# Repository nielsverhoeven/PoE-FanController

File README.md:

# PoE-FanController

A PoE 802.3at (25.5 W) powered quad-fan controller using the **Waveshare ESP32-P4-ETH**
development board (SKU 32086) mounted HAT-style on a custom carrier PCB.  The carrier
handles PoE power extraction and 12 V fan outputs; the Waveshare module integrates the
**ESP32-P4NRW32** SoC, **LAN8720A** Ethernet PHY (RMII), **CH343P** USB-UART bridge,
USB-C connector, and 32 MB flash + 32 MB PSRAM.  Provides wired Ethernet for reliable
data-centre and server-room deployments.

## Key components

| Ref | Part | Function |
|-----|------|----------|
| —   | Waveshare ESP32-P4-ETH (SKU 32086) | MCU module — ESP32-P4NRW32 dual-core RISC-V 400 MHz, LAN8720A PHY, CH343P USB bridge, 32 MB flash, 32 MB PSRAM |
| J8  | Sullins PREC020DAAN-RC / Würth 61304021821 | 2×20 HAT header — carrier PCB ↔ Waveshare module |
| U1  | Ag9905M (Silvertel) | PoE+ PD module — 802.3at Class 4, 12 V isolated output |
| U2  | LM2596S-5.0/NOPB (TI) | Buck regulator — 12 V → 5 V, 3 A |
| D2  | 1N5822 | USB back-feed protection Schottky — prevents back-feeding PC USB host when Waveshare is programmed via USB-C while PoE is live |
| J1  | Würth 615008144521 | Shielded RJ45 — PoE **power** input only; MDI secondary NC |

## Features

- 4 × 12 V PWM fan channels (25 kHz), GPIO4–7
- 4 × tachometer inputs (IRAM_ATTR ISR), GPIO8–11
- NTC thermistor ADC (GPIO16, 12-bit)
- HTTP OTA firmware update via POST `/api/v1/ota`
- Wired Ethernet via Waveshare's built-in LAN8720A (ETH.begin() / RMII)
- PoE 802.3at Class 4 power budget: ~18.9 W consumed; ~1.1 W margin against 20 W cap
- Programming and debug via Waveshare's USB-C connector (CH343P USB-UART bridge)

## Power supply

```
J1 RJ45 (PoE power only, MDI secondary NC)
  → U1 Ag9905M → +12 V
    → J2–J5  fan headers (12 V)
    → U2 LM2596S-5.0 → +5 V → D2 (back-feed) → +5V_HAT (~4.65 V)
      → J8 (2×20 HAT header) → Waveshare ESP32-P4-ETH
        → (internal Waveshare 3.3 V LDO) → +3V3 via J8 → TACH pull-ups, NTC divider
```

> **PSE note:** The PoE switch port connected to J1 must be set to **"force PoE"** mode
> (power regardless of link state), because J1's MDI secondary is NC and no 802.3 Ethernet
> link is visible on that port.  Ethernet data connectivity is provided by the Waveshare
> board's own built-in RJ45 on a separate cable.

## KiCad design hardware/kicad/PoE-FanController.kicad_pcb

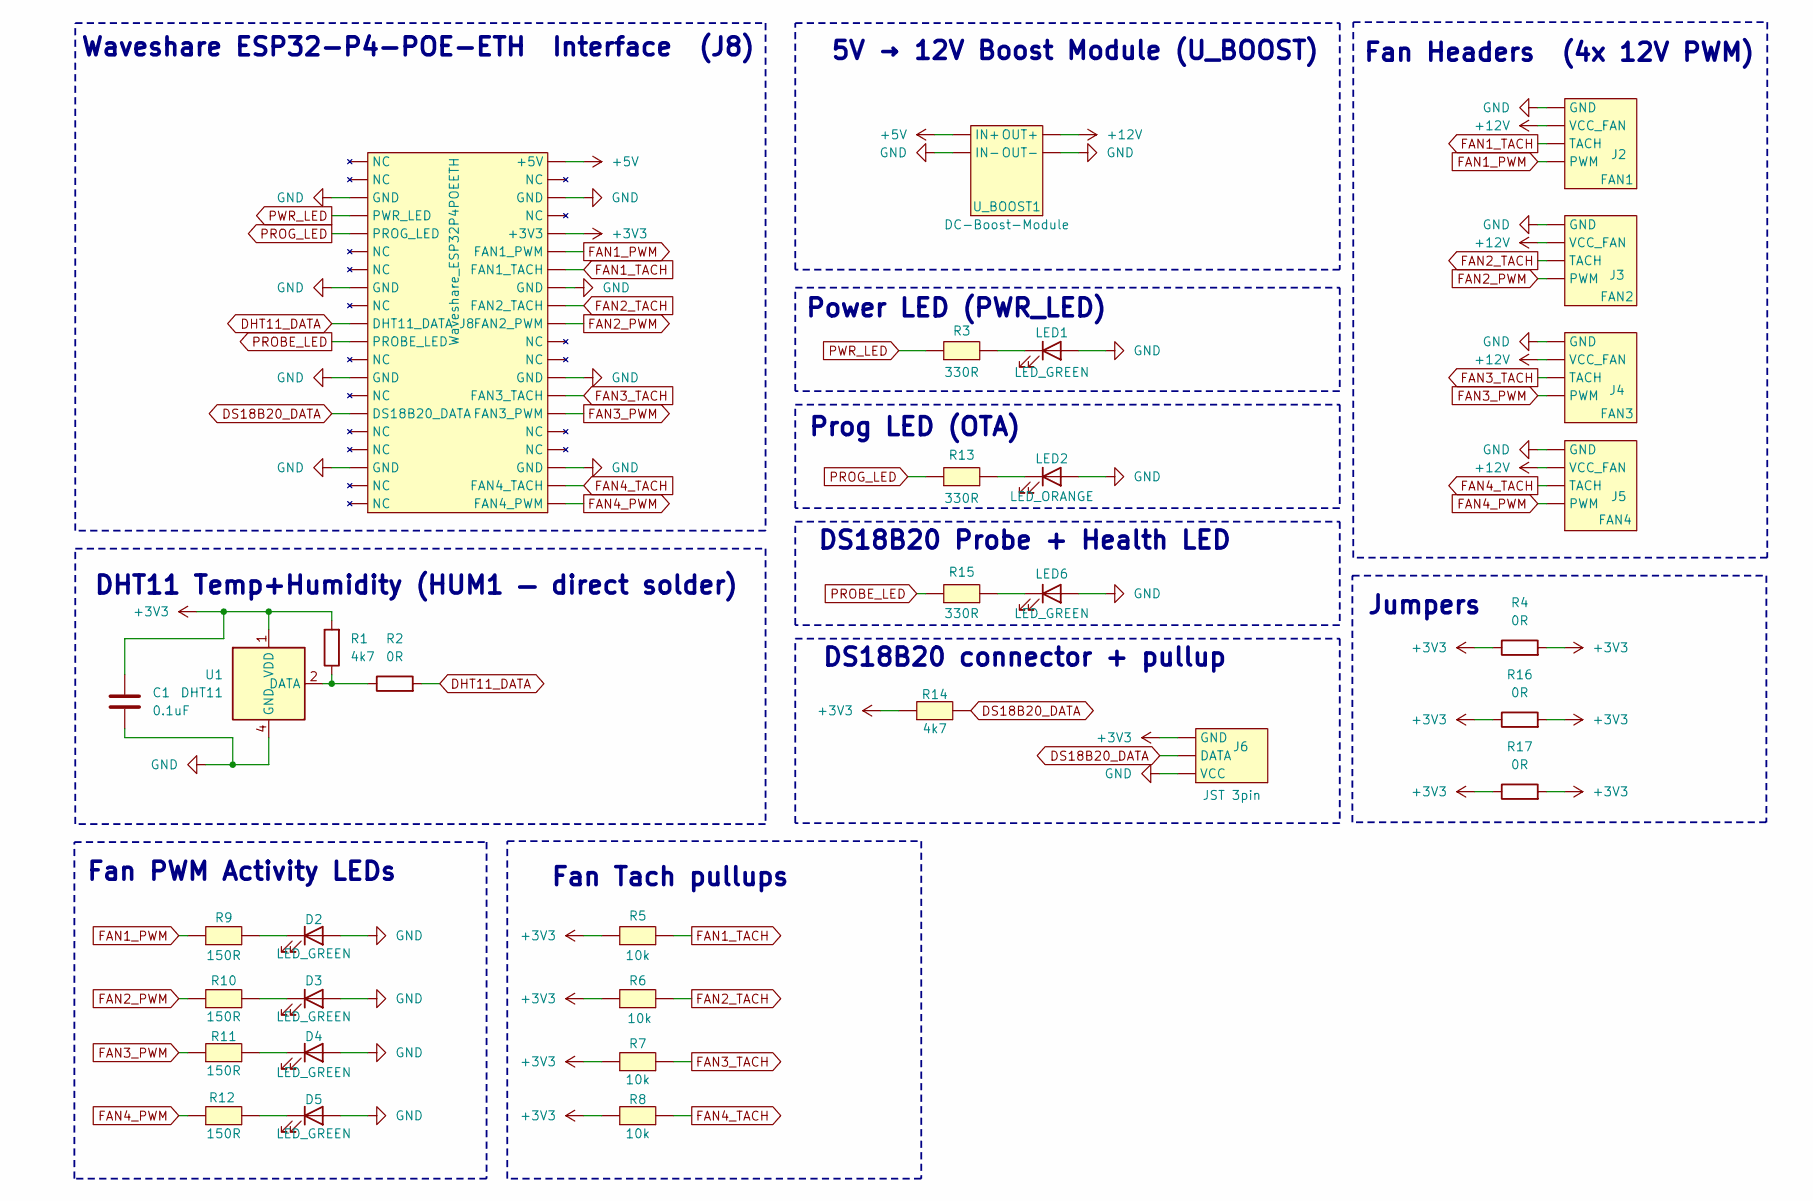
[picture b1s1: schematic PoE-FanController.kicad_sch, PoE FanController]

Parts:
C1: 0.1uF; C_Disc_D5.0mm_W2.5mm_P5.00mm
D2, D3, D4, D5: LED_GREEN; LED_D3.0mm
J2: FAN1; Molex_KK-254_AE-6410-04A_1x04_P2.54mm_Vertical
J3: FAN2; Molex_KK-254_AE-6410-04A_1x04_P2.54mm_Vertical
J4: FAN3; Molex_KK-254_AE-6410-04A_1x04_P2.54mm_Vertical
J5: FAN4; Molex_KK-254_AE-6410-04A_1x04_P2.54mm_Vertical
J6: JST 3pin; JST_EH_B3B-EH-A_1x03_P2.50mm_Vertical
J8: Waveshare_ESP32P4POEETH; ESP32-P4-PoE-ETH-PinSocket
LED1, LED6: LED_GREEN; LED_D3.0mm
LED2: LED_ORANGE; LED_D3.0mm
R1, R14: 4k7; R_Axial_DIN0207_L6.3mm_D2.5mm_P7.62mm_Horizontal
R2, R4, R16, R17: 0R; R_Axial_DIN0207_L6.3mm_D2.5mm_P7.62mm_Horizontal
R3, R13, R15: 330R; R_Axial_DIN0207_L6.3mm_D2.5mm_P7.62mm_Horizontal
R5, R6, R7, R8: 10k; R_Axial_DIN0207_L6.3mm_D2.5mm_P7.62mm_Horizontal
R9, R10, R11, R12: 150R; R_Axial_DIN0207_L6.3mm_D2.5mm_P7.62mm_Horizontal
U1: DHT11; Aosong_DHT11_5.5x12.0_P2.54mm
U_BOOST1: DC-Boost-Module

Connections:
+3V3: C1.1, J6.1 (GND), J8.36 (+3V3), R1.2, R4.1, R4.2, R5.1, R6.1, R7.1, R8.1, R14.1, R16.1, R16.2, R17.1, R17.2, U1.1 (VDD)
+5V: J8.40 (+5V), U_BOOST1.1 (IN+)
+12V: J2.2 (VCC_FAN), J3.2 (VCC_FAN), J4.2 (VCC_FAN), J5.2 (VCC_FAN), U_BOOST1.3 (OUT+)
DS18B20_DATA: J6.2 (DATA), J8.6 (DS18B20_DATA), R14.2
FAN1_PWM: J2.4 (PWM), J8.34 (FAN1_PWM), R9.1
FAN1_TACH: J2.3 (TACH), J8.35 (FAN1_TACH), R5.2
FAN2_PWM: J3.4 (PWM), J8.31 (FAN2_PWM), R10.1
FAN2_TACH: J3.3 (TACH), J8.32 (FAN2_TACH), R6.2
FAN3_PWM: J4.4 (PWM), J8.24 (FAN3_PWM), R11.1
FAN3_TACH: J4.3 (TACH), J8.25 (FAN3_TACH), R7.2
FAN4_PWM: J5.4 (PWM), J8.21 (FAN4_PWM), R12.1
FAN4_TACH: J5.3 (TACH), J8.22 (FAN4_TACH), R8.2
GND: C1.2, D2.2 (A), D3.2 (A), D4.2 (A), D5.2 (A), J2.1 (GND), J3.1 (GND), J4.1 (GND), J5.1 (GND), J6.3 (VCC), J8.3 (GND), J8.8 (GND), J8.13 (GND), J8.18 (GND), J8.23 (GND), J8.28 (GND), J8.33 (GND), J8.38 (GND), LED1.2 (A), LED2.2 (A), LED6.2 (A), U1.4 (GND), U_BOOST1.2 (IN-), U_BOOST1.4 (OUT-)
unnamed: D2.1 (K), R9.2
unnamed: D3.1 (K), R10.2
unnamed: D4.1 (K), R11.2
unnamed: D5.1 (K), R12.2
unnamed: LED1.1 (K), R3.2
unnamed: LED2.1 (K), R13.2
unnamed: LED6.1 (K), R15.2
PROBE_LED: J8.11 (PROBE_LED), R15.1
PROG_LED: J8.16 (PROG_LED), R13.1
PWR_LED: J8.17 (PWR_LED), R3.1

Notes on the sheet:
5V → 12V Boost Module (U_BOOST)
Fan Headers (4x 12V PWM)
Fan PWM Activity LEDs
Power LED (PWR_LED)
Prog LED (OTA)
DHT11 Temp+Humidity (HUM1 — direct solder)
DS18B20 Probe + Health LED
Waveshare ESP32-P4-POE-ETH Interface (J8)
Fan Tach pullups
DS18B20 connector + pullup
Jumpers

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
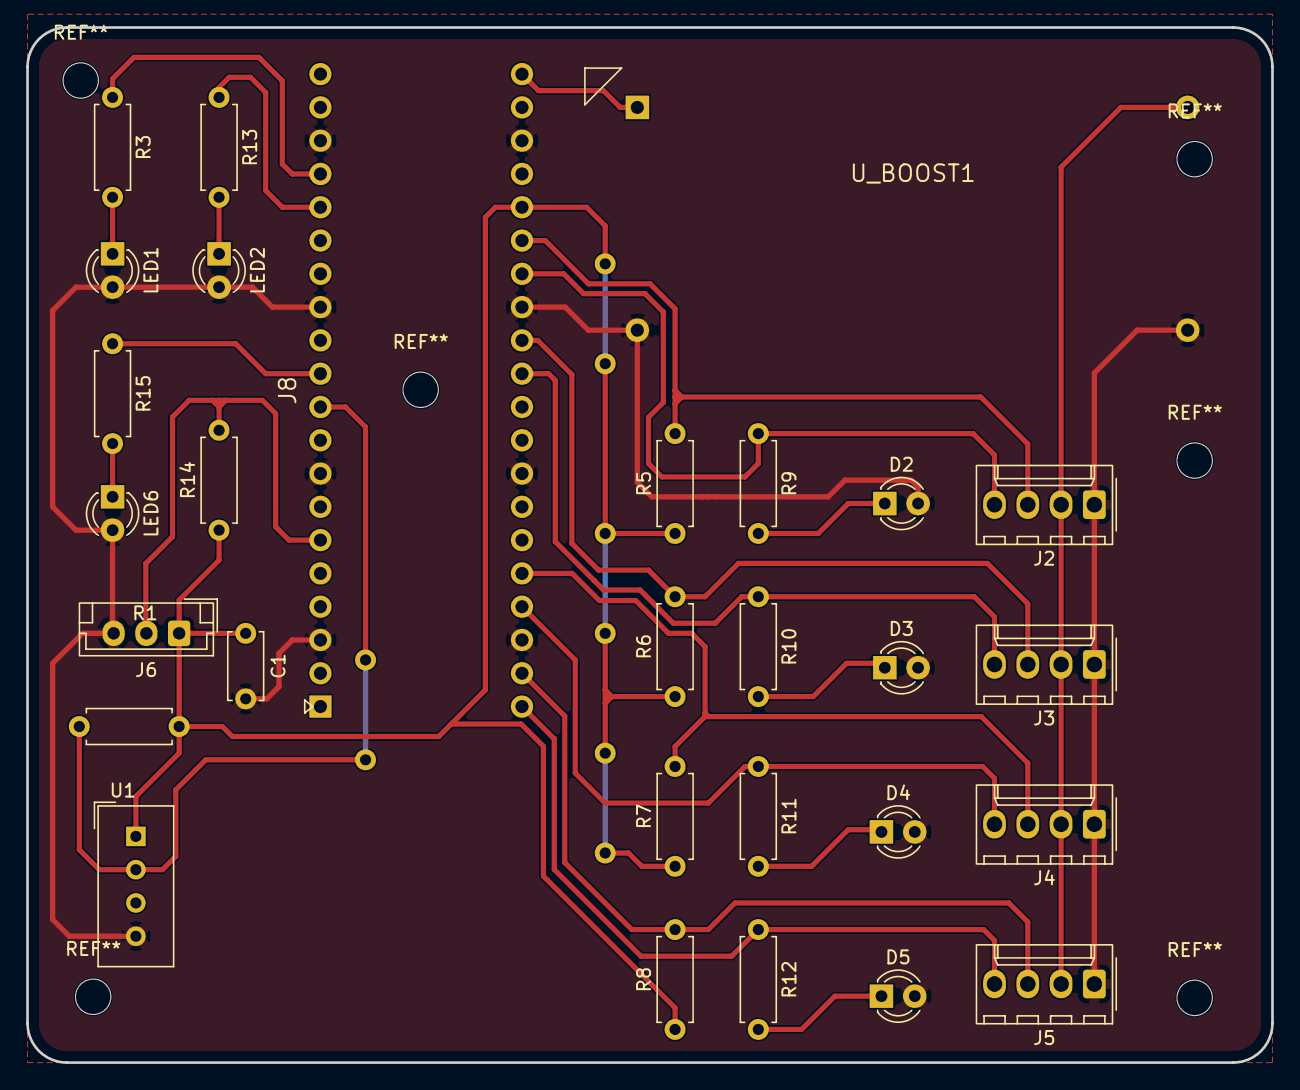
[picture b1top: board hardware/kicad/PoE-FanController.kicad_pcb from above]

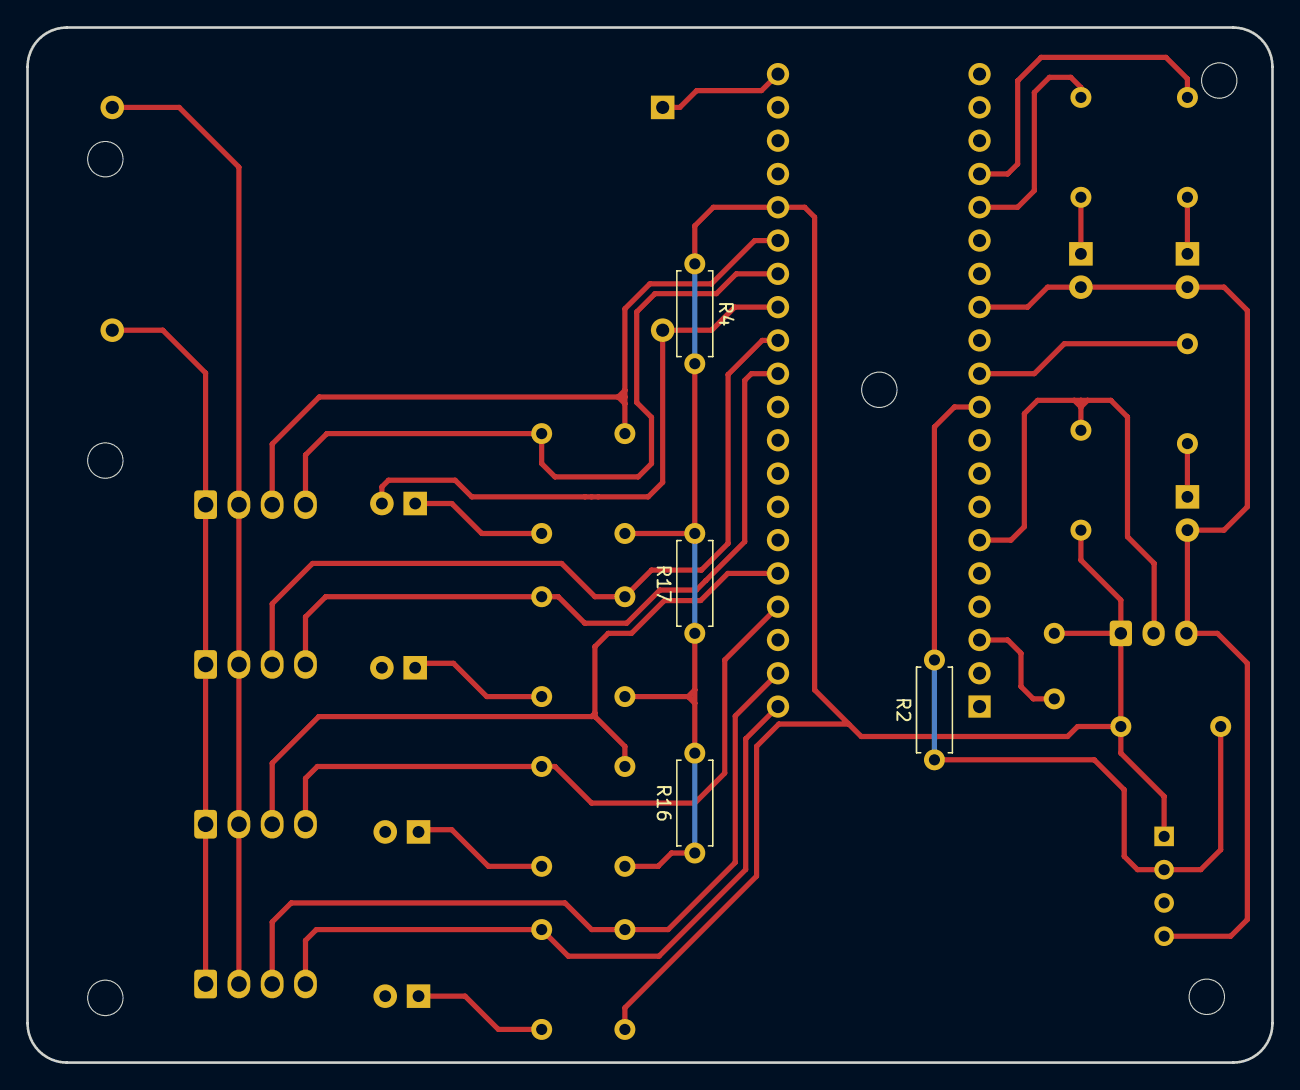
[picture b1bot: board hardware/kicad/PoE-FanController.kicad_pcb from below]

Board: 2 copper layers, 95.0 x 79.0 mm, 33 parts (4 on the bottom side), 24 nets.

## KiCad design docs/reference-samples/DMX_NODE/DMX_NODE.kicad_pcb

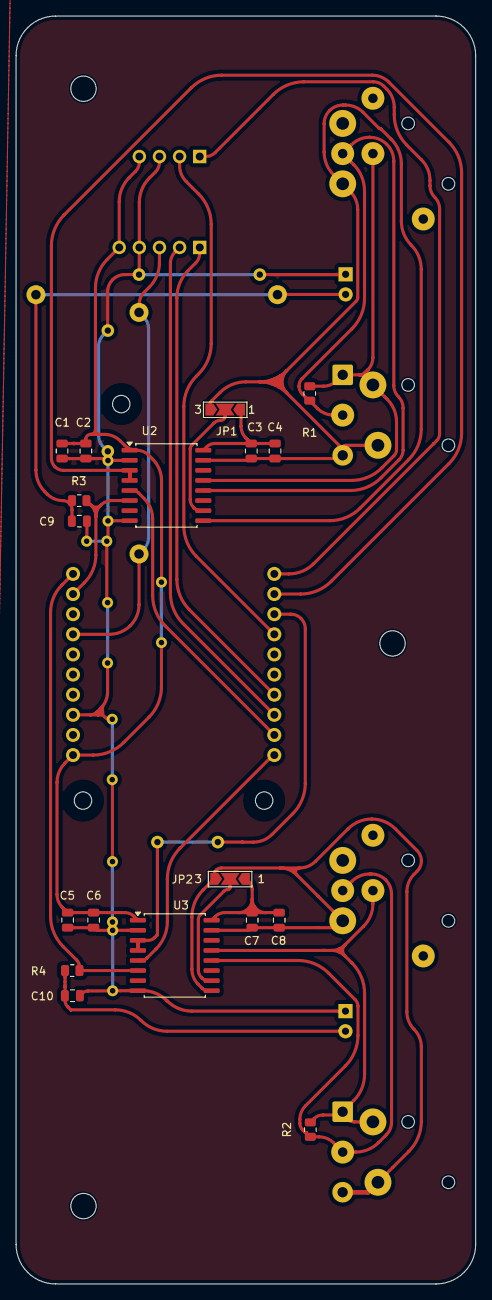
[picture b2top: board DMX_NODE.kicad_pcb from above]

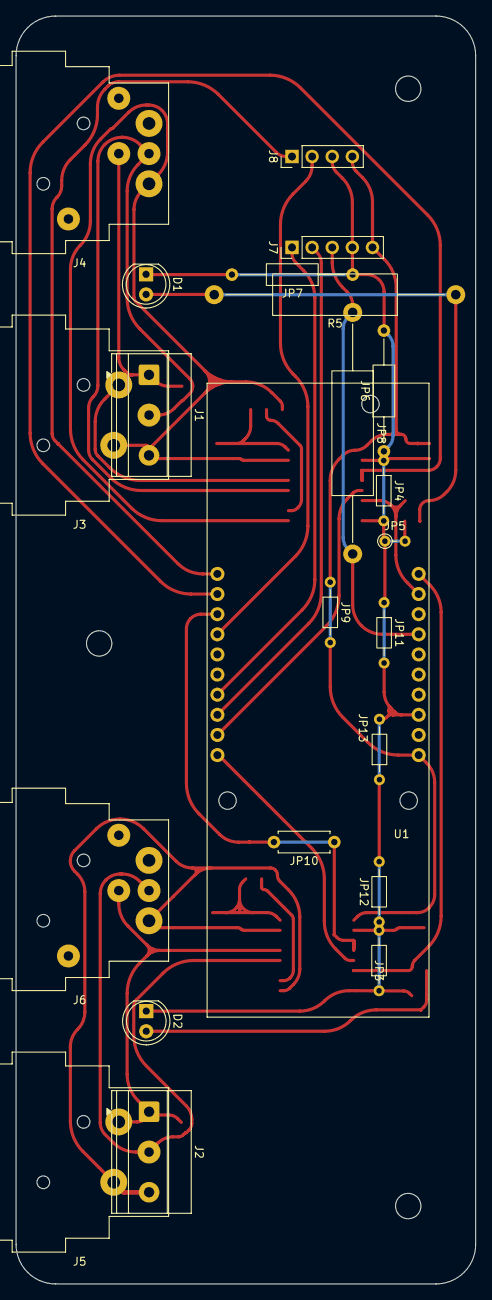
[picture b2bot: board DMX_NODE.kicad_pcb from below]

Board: 2 copper layers, 58.0 x 160.0 mm, 44 parts (26 on the bottom side), 25 nets.

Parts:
C1, C4, C5, C8: 10uF; C_0805_2012Metric
C2, C3, C6, C7: 100nF; C_0805_2012Metric
C9, C10: 4.7uF; C_0805_2012Metric
D1, D2: LED; LED_D5.0mm
J1, J2: DMX_OUT; TerminalBlock_Phoenix_MKDS-1,5-3-5.08_1x03_P5.08mm_Horizont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
J3, J5: XLR3; Jack_XLR_Neutrik_NC3FAAH-0_Horizontal
J4, J6: XLR5; Jack_XLR_Neutrik_NC5FAH-0_Horizontal
J7: ENCODER; PinHeader_1x05_P2.54mm_Vertical
J8: OLED; PinHeader_1x04_P2.54mm_Vertical
JP1, JP2: VISO select; SolderJumper-3_P2.0mm_Open_TrianglePad1.0x1.5mm_NumberLabels
JP3, JP4, JP9, JP11, JP12, JP13: Jumper_2_Bridged; R_Axial_DIN0204_L3.6mm_D1.6mm_P7.62mm_Horizontal
JP5: Jumper_2_Bridged; R_Axial_DIN0204_L3.6mm_D1.6mm_P2.54mm_Vertical
JP6, JP7: Jumper_2_Bridged; R_Axial_DIN0207_L6.3mm_D2.5mm_P15.24mm_Horizontal
JP8: Jumper_2_Bridged; R_Axial_DIN0516_L15.5mm_D5.0mm_P30.48mm_Horizontal
JP10: Jumper_2_Bridged; R_Axial_DIN0207_L6.3mm_D2.5mm_P7.62mm_Horizontal
MH1, MH2, MH3: MountingHole_3.2mm_M3_DIN965
R1, R2: R120; R_0805_2012Metric
R3, R4: 2.2k; R_0805_2012Metric
R5: 0R; R_Axial_DIN0516_L15.5mm_D5.0mm_P30.48mm_Horizontal
U1: ESP32-POE; MODULE_ESP32-POE
U2, U3: CA-IS3092W; SOIC-16W_7.5x10.3mm_P1.27mm

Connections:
DMX_A_EN: U1.EXT2_9 (GPIO14/HS2_CLK), U2.3 (RO), U2.4 (~RE)
DMX_A_RX: U1.EXT2_2 (GPI36/U1RXD), U2.5 (DE)
DMX_A_TX: R3.1, U1.EXT1_9 (GPIO4/U1TXD), U2.6 (DI)
DMX_B_EN: JP10.1 (A), JP10.2 (B), U1.EXT2_8 (GPIO15/HS2_CMD), U3.3 (RO), U3.4 (~RE)
DMX_B_RX: U1.EXT2_1 (GPI39), U3.5 (DE)
DMX_B_TX: R4.1, U1.EXT1_10 (GPIO5/SPI_CS), U3.6 (DI)
ENC_A: J7.1, U1.EXT2_4 (GPI34/BUT1)
ENC_B: J7.2, U1.EXT2_3 (GPI35)
ENC_SW: J7.3, JP8.1 (A), JP8.2 (B), U1.EXT1_7 (GPIO2/HS2_DATA0)
GND1: C1.2, C2.2, C5.2, C6.2, C9.2, C10.2, D1.1 (K), D2.1 (K), J7.4, J8.3, JP3.1 (A), JP3.2 (B), JP4.1 (A), JP4.2 (B), JP5.1 (A), JP5.2 (B), JP6.1 (A), JP6.2 (B), JP7.1 (A), JP7.2 (B), JP11.1 (A), JP11.2 (B), JP12.1 (A), JP12.2 (B), JP13.1 (A), JP13.2 (B), U1.EXT1_3 (GND), U2.2 (GNDA), U2.8 (GNDA), U3.2 (GNDA), U3.8 (GNDA)
GND2: C3.2, C4.2, J1.3, J3.1, J4.1, JP1.3 (B), U2.9 (GNDB), U2.15 (GNDB)
GND3: C7.2, C8.2, J2.3, J5.1, J6.1, JP2.3 (B), U3.9 (GNDB), U3.15 (GNDB)
unnamed: C9.1, D1.2 (A), R3.2, R5.1, R5.2
unnamed: C10.1, D2.2 (A), R4.2
unnamed: JP1.2 (C), U2.10 (SEL)
unnamed: JP2.2 (C), U3.10 (SEL)
PORT1_A: J3.3, J4.3, R1.1, U2.12 (A)
PORT1_B: J1.1, J3.2, J4.2, R1.2, U2.13 (B)
PORT2_A: J5.3, J6.3, R2.1, U3.12 (A)
PORT2_B: J2.1, J5.2, J6.2, R2.2, U3.13 (B)
SCL: J8.2, U1.EXT2_7 (GPIO16/I2C-SCL)
SDA: J8.1, U1.EXT2_10 (GPIO13/I2C-SDA)
VCC: C1.1, C2.1, C5.1, C6.1, J7.5, J8.4, JP9.1 (A), JP9.2 (B), U1.EXT1_1 (+5V), U2.1 (VCC), U3.1 (VCC)
VDC: C7.1, C8.1, JP2.1 (A), U3.16 (VIso)
VDD: C3.1, C4.1, JP1.1 (A), U2.16 (VIso)

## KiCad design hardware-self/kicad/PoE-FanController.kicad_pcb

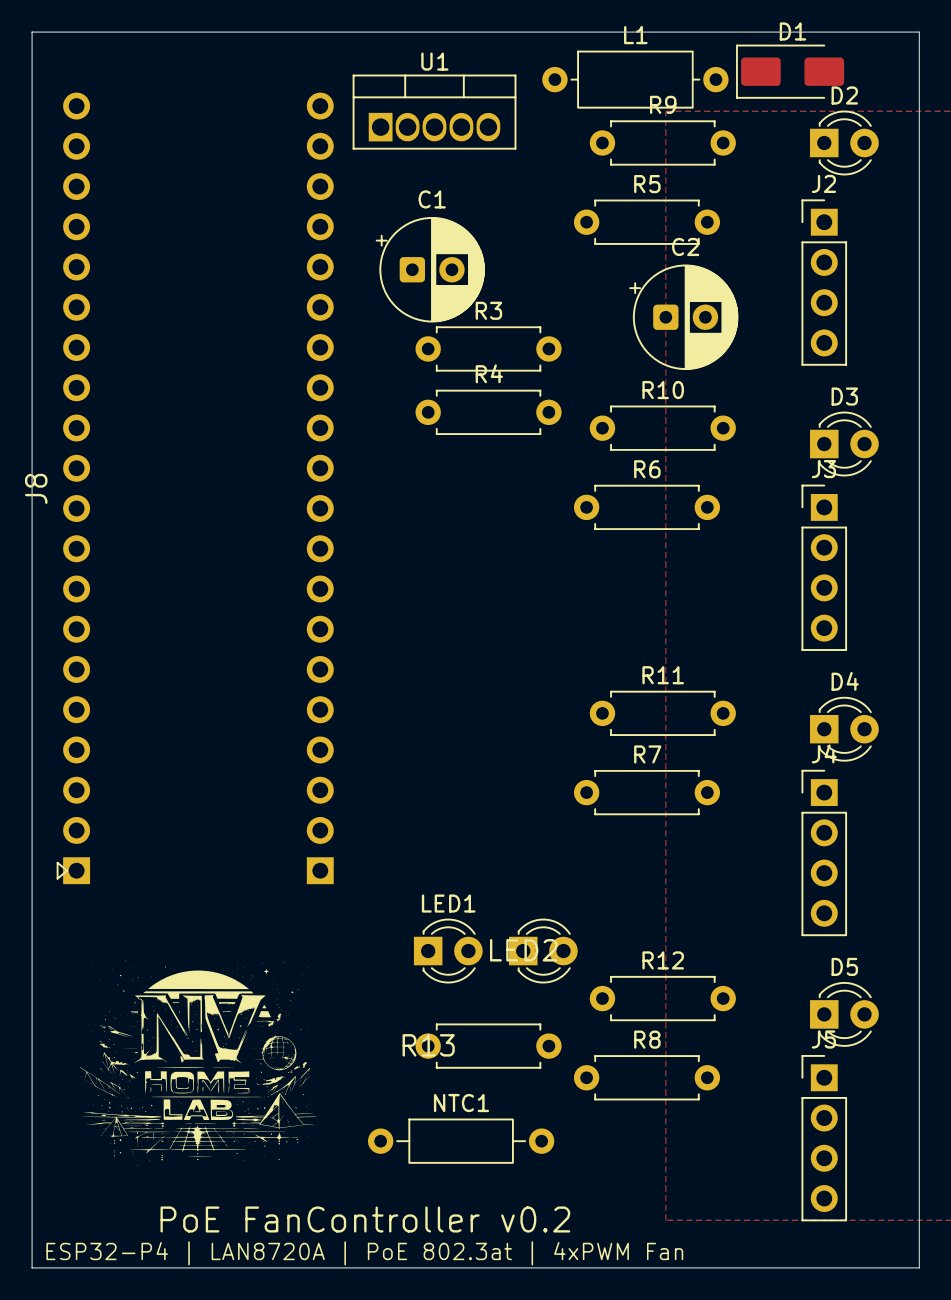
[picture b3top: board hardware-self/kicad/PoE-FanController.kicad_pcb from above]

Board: 2 copper layers, 56.0 x 78.0 mm, 28 parts (0 on the bottom side), 21 nets, no tracks yet.

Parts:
C1, C2: 100uF_25V; CP_Radial_D6.3mm_P2.50mm
D1: SS54; D_SMA
D2, D3, D4, D5: LED_D3.0mm
J2: FAN1; PinHeader_1x04_P2.54mm_Vertical
J3: FAN2; PinHeader_1x04_P2.54mm_Vertical
J4: FAN3; PinHeader_1x04_P2.54mm_Vertical
J5: FAN4; PinHeader_1x04_P2.54mm_Vertical
J8: Waveshare_ESP32P4POEETH; PinSocket_2x20_P2.54mm_P15.38mm_Vertical
L1: 100uH; L_Axial_L7.0mm_D3.3mm_P10.16mm_Horizontal_Fastron_MICC
LED1: LED_GREEN; LED_D3.0mm
LED2: LED_ORANGE; LED_D3.0mm
NTC1: NTC10K_B3950; R_Axial_DIN0207_L6.3mm_D2.5mm_P10.16mm_Horizontal
R3, R13: 330R; R_Axial_DIN0207_L6.3mm_D2.5mm_P7.62mm_Horizontal
R4, R5, R6, R7, R8: 10k; R_Axial_DIN0207_L6.3mm_D2.5mm_P7.62mm_Horizontal
R9, R10, R11, R12: 1k; R_Axial_DIN0207_L6.3mm_D2.5mm_P7.62mm_Horizontal
U1: LM2587-12; TO-220-5_Vertical

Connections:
+3V3: J8.1 (+3V3), J8.17 (+3V3), R4.1, R5.1, R6.1, R7.1, R8.1
+5V: C1.1, J8.2 (+5V), J8.4 (+5V), L1.1, U1.2
+12V: C2.1, D1.2, J2.2 (VCC_FAN), J3.2 (VCC_FAN), J4.2 (VCC_FAN), J5.2 (VCC_FAN), R9.1, R10.1, R11.1, R12.1
/FAN1_IND: D2.1, R9.2
/FAN2_IND: D3.1, R10.2
/FAN3_IND: D4.1, R11.2
/FAN4_IND: D5.1, R12.2
/LED_A: LED1.1 (A), R3.2
/PROG_LED_A: LED2.1, R13.2
BOOST_SW: D1.1, L1.2, U1.3, U1.4
FAN1_PWM: J2.4 (PWM), J8.7 (FAN1_PWM)
FAN1_TACH: J2.3 (TACH), J8.12 (FAN1_TACH), R5.2
FAN2_PWM: J3.4 (PWM), J8.8 (FAN2_PWM)
FAN2_TACH: J3.3 (TACH), J8.13 (FAN2_TACH), R6.2
FAN3_PWM: J4.4 (PWM), J8.10 (FAN3_PWM)
FAN3_TACH: J4.3 (TACH), J8.15 (FAN3_TACH), R7.2
FAN4_PWM: J5.4 (PWM), J8.11 (FAN4_PWM)
FAN4_TACH: J5.3 (TACH), J8.16 (FAN4_TACH), R8.2
GND: C1.2, C2.2, D2.2, D3.2, D4.2, D5.2, J2.1 (GND), J3.1 (GND), J4.1 (GND), J5.1 (GND), J8.6 (GND), J8.9 (GND), J8.14 (GND), J8.20 (GND), J8.25 (GND), J8.29 (GND), J8.33 (GND), J8.38 (GND), LED1.2 (K), LED2.2, NTC1.2, U1.1, U1.5
NTC_ADC: J8.23 (NTC_ADC), NTC1.1, R4.2
STATUS_LED: J8.3 (LED), R3.1

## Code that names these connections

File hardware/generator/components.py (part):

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
Signal assignments (user-specified overhaul):
  Left column (pins 1-20, bottom→top on physical board):
    Pin 6  → DS18B20_DATA (GPIO2, 1-Wire probe data)
    Pin 10 → PROBE_LED    (GPIO5, probe health LED)
    Pin 11 → DHT11_DATA   (GPIO6, DHT11 single-wire)
    Pin 16 → PROG_LED     (GPIO17, OTA/write indicator)
    Pin 17 → PWR_LED      (GPIO18, power-on status LED)
    Pins 3,8,13,18 → GND
    All others → NC

  Right column (pins 21-40, bottom→top on physical board):
    Pin 21 → FAN4_PWM  (GPIO48)
    Pin 22 → FAN4_TACH (GPIO47)
    Pin 24 → FAN3_PWM  (GPIO46)
    Pin 25 → FAN3_TACH (GPIO33)
    Pin 31 → FAN2_PWM  (GPIO23)
    Pin 32 → FAN2_TACH (GPIO22)
    Pin 34 → FAN1_PWM  (GPIO21)
    Pin 35 → FAN1_TACH (GPIO20)
    Pin 36 → +3V3 (SOLE source for pull-ups and sensor VCC)
    Pin 40 → VBUS (+5V, boost module input)
    Pins 23,28,33,38 → GND
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    #
    # CORRECTED ASSIGNMENTS (issue #148 — architecture validation v4.2.1):
    #   Left col  (Row A, pins  1-20): GND on 3,8,13,18;
    #             STATUS_LED/GPIO2 on pin 6; PROG_LED/GPIO15 on pin 14;
    #             DHT11_DATA/GPIO16 on pin 15; DS18B20_DATA/GPIO19 on pin 19.
    #             All others NC.
    #   Right col (Row B, pins 21-40): ALL 8 fan signals here (GPIO20-23,26,27,46,47);
    #             PROBE_LED/GPIO48 on pin 21; +3V3 output on pin 36; +5V/VBUS on pin 40.
    #             FORBIDDEN: pins 25,26 = GPIO33/32 = EMAC_RXD1/RXD0 — left NC.
    #             Reserved: pin 37 = EN, pin 30 = RUN — left NC.
    #
    # SIGNAL ASSIGNMENTS (user overhaul v0.6):
    #   Left col (pins 20→1, TOP→BOTTOM):
    #     Pin 17 → PWR_LED (GPIO18), Pin 16 → PROG_LED (GPIO17)
    #     Pin 14 → DHT11_DATA (GPIO15)
    #     Pin 7  → PROBE_LED (GPIO3),  Pin 6  → DS18B20_DATA (GPIO2)
    #     Pins 3,8,13,18 → GND; all others NC
    #   Right col (pins 40→21, TOP→BOTTOM):
    #     Pin 40 → +5V/VBUS, Pin 36 → +3V3
    #     Pin 34 → FAN1_TACH (GPIO21), Pin 32 → FAN2_PWM (GPIO22)
    #     Pin 27 → FAN3_PWM (GPIO27),  Pin 26 → FAN3_TACH (GPIO32) [EMAC—verify]
    #     Pin 22 → FAN4_PWM (GPIO47),  Pin 21 → FAN4_TACH (GPIO48)
    #     Pins 23,28,33,38 → GND; pins 25,30,37,39 → NC; others NC
    s.define("Custom:J8_Waveshare", "J", "Waveshare_ESP32P4POEETH",
             "Custom:ESP32-P4-PoE-ETH-PinSocket",
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                 ("NC",           "20", "no_connect"),    # GPIO54   — top-left
                 ("NC",           "19", "no_connect"),    # GPIO19   — NC (was DS18B20)
                 ("GND",          "18", "passive"),       # Physical GND
                 ("PWR_LED",      "17", "output"),        # GPIO18   — power-on status LED
                 ("PROG_LED",     "16", "output"),        # GPIO17   — OTA/write LED
                 ("NC",           "15", "no_connect"),    # GPIO16   — NC (was DHT11)
                 ("NC",           "14", "no_connect"),    # GPIO15   — NC (was DHT11)
                 ("GND",          "13", "passive"),       # Physical GND
                 ("NC",           "12", "no_connect"),    # GPIO14   — NC
                 ("DHT11_DATA",   "10", "input"),         # GPIO5    — DHT11 single-wire
                 ("PROBE_LED",    "11", "output"),        # GPIO6    — probe health LED
                 ("NC",           "9",  "no_connect"),    # GPIO4    — NC
                 ("GND",          "8",  "passive"),       # Physical GND
                 ("NC",           "7",  "no_connect"),    # GPIO3    — NC (was PROBE_LED)
                 ("DS18B20_DATA", "6",  "bidirectional"), # GPIO2    — 1-Wire probe data
                 ("NC",           "5",  "no_connect"),    # SCL/GPIO8 — NC
                 ("NC",           "4",  "no_connect"),    # SDA/GPIO7 — NC
                 ("GND",          "3",  "passive"),       # Physical GND
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                 ("GND",          "38", "passive"),       # Physical GND
                 ("NC",           "37", "no_connect"),    # EN       — chip-enable RESERVED
                 ("+3V3",         "36", "power_out"),     # +3V3     — SOLE 3.3V source
                 ("FAN1_PWM",     "34", "output"),        # GPIO21   — FAN1 speed control (J8 pin 34)
                 ("FAN1_TACH",    "35", "input"),          # GPIO20   — FAN1 tach IRQ   (J8 pin 35)
                 ("GND",          "33", "passive"),       # Physical GND
                 ("FAN2_TACH",    "32", "input"),         # GPIO22   — FAN2 tach IRQ   (J8 pin 32)
                 ("FAN2_PWM",     "31", "output"),        # GPIO23   — FAN2 speed control (J8 pin 31)
                 ("NC",           "30", "no_connect"),    # RUN      — system control RESERVED
                 ("NC",           "29", "no_connect"),    # GPIO26   — NC
                 ("GND",          "28", "passive"),       # Physical GND
                 ("FAN3_TACH",    "25", "input"),         # GPIO33   — FAN3 tach IRQ   (J8 pin 25)
                 ("FAN3_PWM",     "24", "output"),        # GPIO46   — FAN3 speed control (J8 pin 24)
                 ("NC",           "27", "no_connect"),    # GPIO27   — NC (was FAN3_TACH)
                 ("NC",           "26", "no_connect"),    # GPIO32   — NC (was FAN3_PWM)
                 ("GND",          "23", "passive"),       # Physical GND
                 ("FAN4_TACH",    "22", "input"),         # GPIO47   — FAN4 tach IRQ   (J8 pin 22)
                 ("FAN4_PWM",     "21", "output"),        # GPIO48   — FAN4 speed control (J8 pin 21)
             ])

    # 4-pin fan header (J2-J5) — all pins on LEFT side (connector opens left)
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             pins_right=[])

    # 3-pin Molex KK 254 connector — J6 DS18B20 temperature probe header
    # Pin 1: GND, Pin 2: DS18B20_DATA (1-Wire), Pin 3: +3V3 (power to probe)
    # Molex 22-01-3037 / KK-254 3-position housing
    s.define("Custom:Conn_1x03", "J", "Connector_1x03",
             "Connector_Molex:Molex_KK-254_AE-6410-03A_1x03_P2.54mm_Vertical",
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        s.power("GND",          *pd["2"])             # right pin — cathode → GND

    # -----------------------------------------------------------------------
    # PWR_LED circuit: GPIO18 (J8 pin 17) → R3 → LED1 → GND
    # Power-on status indicator. Renamed from STATUS_LED.
    # -----------------------------------------------------------------------
    s.text("Power LED (PWR_LED)", 128, 215, size=2.54, bold=True, color=BLUE)
    p1 = s.component("Custom:R", "R3", "330R", "Resistor_THT:R_Axial_DIN0207_L6.3mm_D2.5mm_P7.62mm_Horizontal",
                     SMALL_CX, LED_CY)
    s.global_label("PWR_LED", *p1["1"], shape="input", angle=180)  # left pin
    s.label("LED_A",           *p1["2"])                             # right pin

    p1 = s.component("Custom:LED", "LED1", "LED_GREEN", "LED_THT:LED_D3.0mm",
                     LARGE_CX, LED_CY)
    s.label("LED_A", *p1["1"], angle=180)
    s.power("GND",   *p1["2"])

    # -----------------------------------------------------------------------
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    s.text("Prog LED (OTA)", 128, 233, size=2.54, bold=True, color=BLUE)
    p1 = s.component("Custom:R", "R13", "330R", "Resistor_THT:R_Axial_DIN0207_L6.3mm_D2.5mm_P7.62mm_Horizontal",
                     SMALL_CX, PROG_LED_CY)
    s.global_label("PROG_LED", *p1["1"], shape="input", angle=180)
    s.label("PROG_LED_A",      *p1["2"])

    p1 = s.component("Custom:LED", "LED2", "LED_ORANGE", "LED_THT:LED_D3.0mm",
                     LARGE_CX, PROG_LED_CY)
    s.label("PROG_LED_A", *p1["1"], angle=180)
    s.power("GND",        *p1["2"])

    # -----------------------------------------------------------------------
    # DHT11 Temperature + Humidity Sensor (HUM1) — direct solder (3 pins)
    # No breakout module — solder DHT11 legs directly to the 3 PCB pads.
    # Pins: VCC (+3V3) | DATA (DHT11_DATA) | GND
    # Footprint: Custom:DHT11_Direct (generated by gen_footprint_dht11.py)
    # -----------------------------------------------------------------------
    s.text("DHT11 Temp+Humidity (HUM1 — direct solder)", 128, 251, size=2.54, bold=True, color=BLUE)
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                     "Custom:DHT11_Direct",
                     HUM1_CX, DHT11_CY)
    s.power("+3V3",                *p1["1"])
    s.global_label("DHT11_DATA",   *p1["2"], shape="bidirectional")
    s.power("GND",                 *p1["3"])

    # -----------------------------------------------------------------------
    # DS18B20 Temperature Probe + Probe Health LED  (J6 / R14 / R15 / LED6)
    #
    # DS18B20_DATA is GPIO2 (J8 left pin 6).
    # PROBE_LED    is GPIO3 (J8 left pin 7) — LED directly above J6 on PCB.
    #
    # J6 (Molex KK-254, 3-pin):  GND | DS18B20_DATA | +3V3
    # R14 (4.7kΩ): pull-up DS18B20_DATA → +3V3  (1-Wire spec)
    # R15 (330Ω) + LED6: PROBE_LED → LED → GND  (probe health indicator)
    # -----------------------------------------------------------------------
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                     "Resistor_THT:R_Axial_DIN0207_L6.3mm_D2.5mm_P7.62mm_Horizontal",
                     SMALL_CX, PROBE_SENSOR_CY)
    s.power("+3V3",                *p1["1"])
    s.global_label("DS18B20_DATA", *p1["2"], shape="bidirectional")

    # J6 — DS18B20 probe connector
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
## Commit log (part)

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2026-06-06 docs(feature/1): add task breakdown for pcb-connector-edge
2026-06-06 Add KiCad project and board files for PoE Fan Controller
    - Created a new project file `PoE-FanController.kicad_pro` with updated design settings, rules, and ERC configurations.
    - Added a new board file `PoE-FanController.kicad_prl` to define board layout and visibility settings.
    - Enhanced net settings and component class settings for better organization and management.
    - Updated schematic settings including BOM export configurations and drawing parameters.
2026-06-06 feat: add .gitignore for KiCad project files
2026-06-06 docs: add technical plan for issue #13 (missing passive footprints)
2026-06-06 docs: add task breakdown for issue #13 (pcb-passive-footprints)
    T001-T009 dependency-ordered tasks covering ERC gate, Zone A/B/C SMD
    placements, Zone C THT placements (corrected coordinates from architecture
    validation), DRC gate, BOM update, Gerber regeneration, and PR.
    GitHub issues: #18 #14 #16 #15 #17 #21 #20 #19 #22 (children of #13)
2026-06-06 gitignore: add missing report files for DRC and ERC checks
2026-06-06 feat: update KiCad project file with new design settings and rules
2026-06-06 updated gitignore to ignore .history folders created by vscode when using the local history extension
2026-06-06 docs: add feature plan for schematic-readability (#25)
    Documents the completed implementation from PR #24:
    - global_label format decisions and shape selection rationale
    - Isolated GND/GND_PRI domain design
    - power_out default eliminating need for PWR_FLAG symbols
    - Ag9905M VPORT passive pin type change rationale
    - Blue bold 2.54mm section header style
2026-06-06 docs: add task breakdown for schematic-readability feature (#25)
2026-06-06 test(hw): add HW-01..HW-08 validation results for issue #25 schematic-readability
    All 8 hardware gates PASS on feature/25-schematic-readability:
    - HW-01: Generator exit 0; 4 output files written
    - HW-02: ERC 0 error-severity violations (85 warnings, pre-existing)
    - HW-03: 41 global_labels >= 14
    - HW-04: 6 GND_PRI matches >= 2
    - HW-05: 5 blue section headers (color 0 0 255) >= 5
2026-06-06 docs(ci-fixes): add tasks.md with dependency-ordered child issues #34-#38
    Breaks down parent issue #33 into 5 child tasks:
    T001 #34 — Node.js 24 stopgap + action pin upgrades (URGENT: deadline 2026-06-16)
    T002 #35 — Fix hardware-check.yml: Docker KiCad, hard-fail ERC/DRC, timeouts, if:always() uploads
    T003 #36 — Replace release.yml: KiCad fab workflow, zero-tolerance DRC gate, gh release CLI
    T004 #37 — Fix copilot-setup-steps.yml: remove invalid Node.js steps, Python smoke-test, timeout
    T005 #38 — Verify CI, document DRC baseline (C1), open DRC follow-up issue
2026-06-07 Refactor code structure for improved readability and maintainability
2026-06-07 docs: add ESP32-P4 migration technical plan for issue #40
    Creates docs/features/esp32-p4-migration/plan.md — a comprehensive
    MAJOR hardware revision plan covering:
    - Phase 0: Constitution v2.0.0 MAJOR amendment (prerequisite gate)
    - Phase 1: Component selection research (ESP32-P4-MINI-1U, LAN8720A)
    - Phase 2: Schematic changes in generate_project.py (new symbols,
    GPIO re-map, Ethernet PHY addition, J1 RJ45 data-path wiring,
2026-06-07 test(native): add -std=c++11 flag to [env:native] build_flags
    MinGW32 GCC 5.1.0 (toolchain-gccmingw32@1.50100.0) defaults to C++98
    which does not support nullptr. The test_ota.cpp test uses nullptr in two
    ota_upload_handler() calls (lines 99 and 111) which is valid C++11 syntax.
    Fix: add -std=c++11 to [env:native] build_flags so the MinGW32 toolchain
    compiles in C++11 mode. This does NOT affect [env:esp32-p4] which uses
    the arduino-esp32 framework (IDF 5.x, C++14/17 by default).
2026-06-07 test-results: Stage 6 validation report for issue #40 (ESP32-P4 migration)
    All locally-executable Stage 6 checks PASS:
    - 4x YAML workflow files: syntactically valid
    - generate_project.py: py_compile exit 0
    - ERC: 0 error-severity violations (106 warnings, all non-blocking)
    - DRC: 36 violations (local KiCad 10.0.3) <= 76 Docker baseline
    - platformio.ini: custom board esp32-p4-mini-1u with correct 16MB flash
2026-06-07 docs: feature plan for generator-refactor (issue #62)
    Add docs/features/generator-refactor/spec.md and plan.md.
    spec.md: 10 functional requirements, 5 non-functional requirements,
    10 success criteria mapping to issue AC-1..AC-10.
    plan.md: 4-phase implementation plan —
    Phase 0: constitution amendment (P-KI-07 new; P-KI-04, P-HW-05,
    §2.1, §7A scoped to schematic only)
2026-06-07 docs(generator-refactor): add tasks.md with T001-T010 breakdown for #62
    - 10 tasks mapped across Firmware: Module, Firmware: Config,
    Unit Tests, and Documentation layers
    - Dependency graph: T001+T002 ready immediately; T003/T005/T006
    after T002; T004 after T002+T003; T007 after all module tasks;
    T008+T009 after T007; T010 after T008+T009
    - GitHub issues #63-#72 created as child issues of parent #62
2026-06-08 ci: update DRC baseline 76->75 for Waveshare carrier redesign (v2.0.0)
2026-06-08 test: Stage 6 validation results for v2.0.0 Waveshare ESP32-P4-ETH carrier board redesign (Issue #62)
    - Schematic generator: PASS (exit 0, produces .kicad_sch + bom.csv)
    - Generator py_compile: PASS (all 5 modules OK)
    - BOM validation: PASS (U3/U4/U5/J6 absent; U2=LM2596S-5.0, D2=1N5822, J8=HAT header)
    - Schematic content: PASS (8/8 checks: J8 present, LAN8720A/CH340C/ESP32-P4-MINI-1U absent)
    - Board JSON: PASS (waveshare-esp32-p4-eth.json, 32MB flash, 400MHz)
    - platformio.ini: PASS (default_envs=esp32-p4-eth, board=waveshare-esp32-p4-eth)
2026-06-08 docs: update DESIGN.md and README for Waveshare ESP32-P4-ETH carrier board (v2.0.0)
2026-06-08 refactor: update design settings and rules in PoE-FanController.kicad_pro
2026-06-08 hw(pcb): add initial KiCad project files for PoE Fan Controller
2026-06-08 fix: add missing lock file to .gitignore for KiCad PCB
2026-06-08 docs: add PoE Fan Controller diagram and remove outdated PCB sketch
2026-06-08 Implement code changes to enhance functionality and improve performance
2026-06-08 hw: simplify project configuration by removing unused settings and updating version numbers
2026-06-08 docs(kb): update PoE_FanController diagram
2026-06-08 docs: add feature spec and technical plan for DS18B20 temperature probe (#97)
    - spec.md: full feature spec with 13 FRs, NFRs, success criteria,
    out-of-scope list, and assumptions
    - plan.md: technical plan covering hardware schematic/PCB changes,
    GPIO pin selection (GPIO19 = DS18B20_DATA, GPIO20 = PROBE_LED),
    new probe firmware module design, web API extension, testing strategy,
    risk register, and 8-phase implementation roadmap
2026-06-08 feat(ds18b20): add architecture documentation for DS18B20 temperature probe feature
2026-06-08 feat(ds18b20): extend GPIO assignments for DS18B20 temperature probe and status LED
2026-06-08 docs: Create Stage 4 task breakdown for issue #97 (DS18B20 probe feature)
    - Generate 18 dependency-ordered tasks spanning hardware (schematic, ERC, layout, DRC, BOM) and firmware (modules, config, web UI, tests)
    - Map task IDs T001-T018 to GitHub issues #101-#118
    - Link all task issues as children of parent feature issue #97
    - Include detailed task descriptions, acceptance criteria, and dependency chain
    - Task execution spans both hardware design (KiCad) and firmware development (C++, FreeRTOS)
    - Constitution v3.3.0 prerequisite (GPIO19/GPIO20 registration) already satisfied in Stage 3
2026-06-09 fix(docs): update constitution version and amend J2–J5 BOM to keyed headers
2026-06-09 docs: add architecture notes for keyed fan headers (J2–J5) feature
2026-06-09 docs(#100): add task breakdown and GitHub sub-issues for keyed fan headers (T001-T009, issues #120-#128)
2026-06-09 docs: add feature plan for esp32-p4-eth pin layout fix (#133)
    Adds docs/features/esp32-p4-eth-pin-layout/plan.md to the
    bugfix/133-esp32-p4-eth-pin-layout branch.
    Root cause identified: Custom:J8_Waveshare symbol in components.py
    uses PICO-style alternating pin numbers (odd=left, even=right) but
    the Waveshare ESP32-P4-POE-ETH physical module uses consecutive row
    numbering (pins 1-20 on left, 21-40 on right). The footprint
2026-06-09 docs: add tasks breakdown for feature #135 (DHT11 sensor replacement)
2026-06-09 feat: Replace NTC1 Thermistor with DHT11 Sensor
    - Completed implementation of DHT11 temperature and humidity sensor in place of NTC1 thermistor.
    - Updated firmware to utilize adafruit/DHT library; modified `temp` module to include humidity reporting.
    - Renamed GPIO16 net from NTC_ADC to DHT11_DATA; updated schematic and PCB layout accordingly.
    - Verified all acceptance criteria met, including successful ERC/DRC validation and CI checks.
    - Documented changes in test results and updated constitution to v4.1.0.
2026-06-09 hw: add feature spec and technical plan for PCB full routing (issue #83)
    - docs/features/route-pcb-traces/spec.md — functional requirements,
    non-functional requirements, success criteria, and out-of-scope
    declarations for the complete PCB routing task
    - docs/features/route-pcb-traces/plan.md — eight-phase implementation
    plan: GND zone net reassignment (Phase 1 pcbnew script), power rails
    (Phase 2), BOOST_SW EMI-critical loop (Phase 3), PWM/TACH/sensor/LED
2026-06-09 docs: create tasks.md for PCB routing feature #83 with 9 dependency-ordered tasks
2026-06-09 hw: add architecture document for PCB trace routing feature with validation matrix and mandatory corrections
2026-06-10 docs(tasks): create task breakdown for issue #148 (correct GPIO pin assignments)
    Create comprehensive dependency-ordered task list for issue #148:
    - T001 (#149): Update schematic generator with correct J8 pin assignments
    - T002 (#151): Run ERC and fix any errors
    - T003 (#152): Sync PCB pad net assignments
    - T004 (#153): Route all PCB traces on correct right-column layout
    - T005 (#154): Run DRC and verify clean
2026-06-10 docs(#148): update plan.md and spec.md for v2 scope (re-run 2026-06-10)
    - Mark T4 (Route PCB Traces) as OUT OF SCOPE explicitly in both files
    - Add T002: footprint rename Custom:PinSocket_2x20_P2.54mm_P15.38mm_Vertical
    -> Custom:ESP32-P4-PoE-ETH-PinSocket across all generator files and .kicad_mod
    - Capture additional pin errors confirmed by 2026-06-10 audit:
    - Pin 2 (left): +5V -> NC (DM/GPIO24, not a power pin)
    - Pin 4 (left): +5V -> NC (SDA/GPIO7, not a power pin)
2026-06-10 docs(#148): Stage 3 re-validation — footprint rename PATCH + architecture update
    Constitution v4.2.1 (PATCH):
    - §2.2 J8 BOM: rename footprint Custom:PinSocket_2x20_P2.54mm_P15.38mm_Vertical
    -> Custom:ESP32-P4-PoE-ETH-PinSocket; correct stale role description
    - P-HW-03 exception note: same footprint rename applied
    - §10 Amendment History: v4.2.1 row added
    architecture.md (Stage 3 re-run):
2026-06-10 docs(tasks): re-scope tasks.md for #148 Stage 4 re-run
    - Add T002: footprint rename (Custom:PinSocket_2x20 -> Custom:ESP32-P4-PoE-ETH-PinSocket) as new GitHub issue #156
    - Update T001 (#149): add pin errors 2, 4, 20 to the fix list
    - Renumber tasks: T002=footprint rename (#156), T003=ERC (#151), T004=PCB sync (#152)
    - Remove T004 route traces (issue #153 closed; routing is out of scope)
    - Update T005 (#154): airwires are NOT a DRC failure gate
    - Update T006 (#155): reflect correct sub-task issue list including #156
2026-06-11 fix(sch/pcb): update column widths for net inspector panel
2026-06-14 docs: add feature spec and technical plan for replace-boost-module (#177)
2026-06-14 docs: constitution v5.0.0 — MAJOR amendment: replace discrete boost stage with DC-DC module (#177)
    - §2.2 U_BOOST BOM row: locked to Amazon.nl B0D9VJKD1L (4-pin 2.54mm THT,
    footprint Custom:DC-Boost-Module); discrete stage U1/L1/D1/C1/C2 retired
    - P-HW-04 right zone: updated to reference U_BOOST module (not U1+L1+D1+C1+C2)
    - §5.1 power chain: rewrote stale content; updated to current daughter-board arch
    - §5.2 power budget: ~19.4W total / 0.6W (3%) margin; VBUS current risk flagged
    - §8.4 bring-up checklist: updated for U_BOOST module steps
2026-06-14 docs: add tasks.md for feature #177 replace-boost-module (9 tasks, issues #178-#186)

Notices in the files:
docs/reference-samples/DMX_NODE/DMX_NODE.kicad_pcb:
© 2026 KC Labs
